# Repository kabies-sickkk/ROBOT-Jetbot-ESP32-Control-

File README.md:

# ROBOT-Jetbot-ESP32-Control-
Báo cáo đồ án môn học Đồ án IoT

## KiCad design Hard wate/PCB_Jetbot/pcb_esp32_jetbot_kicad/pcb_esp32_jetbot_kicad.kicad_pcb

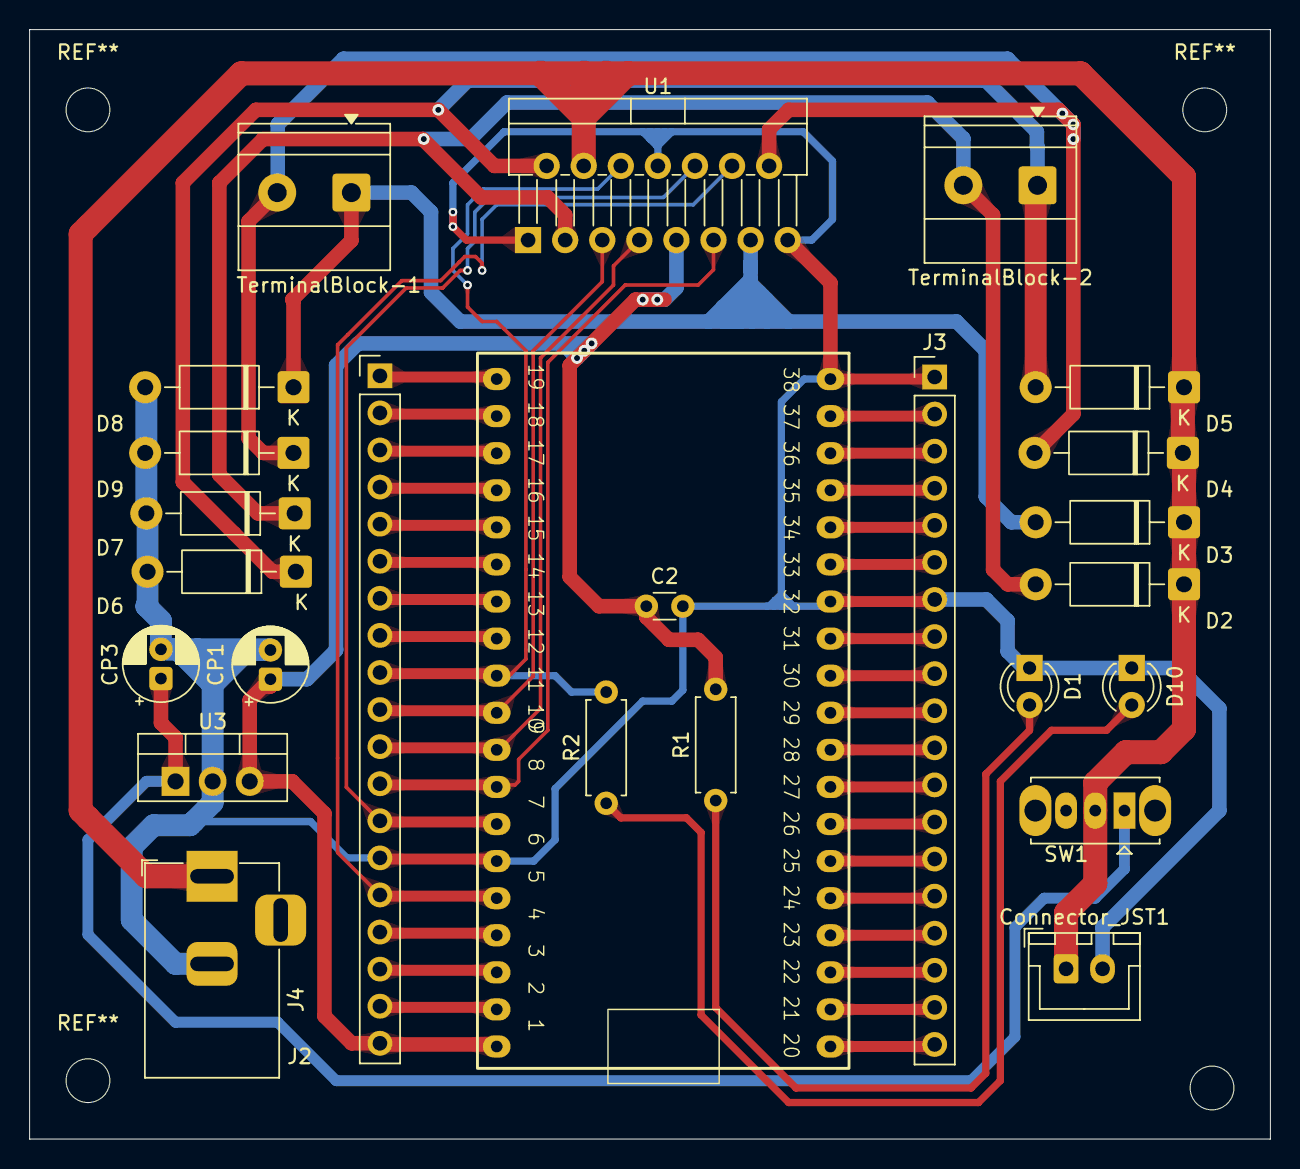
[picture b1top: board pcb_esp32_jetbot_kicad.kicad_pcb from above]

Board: 2 copper layers, 85.0 x 76.0 mm, 25 parts (0 on the bottom side), 44 nets.

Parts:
C2: 0.1uF; C_Disc_D3.0mm_W1.6mm_P2.50mm
CP1, CP3: 100uF; CP_Radial_D5.0mm_P2.00mm
Connector_JST1: JST_XH_2pin; JST_XH_B2B-XH-A_1x02_P2.50mm_Vertical
D1, D10: LED; LED_D3.0mm
D2, D3, D4, D5, D6, D7, D8, D9: D; D_DO-41_SOD81_P10.16mm_Horizontal
J2, J3: Conn_01x19_Socket; PinHeader_1x19_P2.54mm_Vertical
J4: Barrel_Jack_Switch; BarrelJack_Horizontal
R1, R2: 220Ω; R_Axial_DIN0207_L6.3mm_D2.5mm_P7.62mm_Horizontal
SW1: SW_SPDT; SW_Slide_SPDT_Straight_CK_OS102011MS2Q
TerminalBlock-1, TerminalBlock-2: Conn_01x02; TerminalBlock_Phoenix_MKDS-1,5-2-5.08_1x02_P5.08mm_Horizont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
U1: L298N; TO-220-15_P2.54x5.08mm_StaggerOdd_Lead4.58mm_Vertical
U2: ESP32-DevKitC-38; ESP32_38pin
U3: LM7805_TO220; TO-220-3_Vertical

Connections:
+3V3: J2.1, U2.19 (3.3v)
+5V: C2.1, CP1.1, J2.19, R1.2, U1.9 (Vss), U2.1 (5v), U3.3 (VO)
EN: J2.2, U2.18 (EN)
GND: C2.2, CP1.2, CP3.2, Connector_JST1.2, D1.1 (K), D6.2 (A), D7.2 (A), D8.2 (A), D9.2 (A), D10.1 (K), J2.14, J3.1, J3.7, J4.2, U1.1 (SENSE_A), U1.8 (GND), U1.15 (SENSE_B), U2.6 (GND), U2.32 (GND), U2.38 (GND), U3.2 (GND)
GPIO0: J3.14, U2.25 (GPIO0)
GPIO2: J3.15, U2.24 (GPIO2)
GPIO4: J3.13, U2.26 (GPIO4)
GPIO5: J3.10, U2.29 (GPIO5)
GPIO6: J3.19, U2.20 (GPIO6)
GPIO7: J3.18, U2.21 (GPIO7)
GPIO8: J3.17, U2.22 (GPIO8)
GPIO9: J2.16, U2.4 (GPIO9)
GPIO10: J2.17, U2.3 (GPIO10)
GPIO11: J2.18, U2.2 (GPIO11)
GPIO12: J2.13, U1.10 (IN3), U2.7 (GPIO12)
GPIO13: J2.15, U1.12 (IN4), U2.5 (GPIO13)
GPIO14: J2.12, U1.11 (EnB), U2.8 (GPIO14)
GPIO15: J3.16, U2.23 (GPIO15)
GPIO16: J3.12, U2.27 (GPIO16)
GPIO17: J3.11, U2.28 (GPIO17)
GPIO18: J3.9, U2.30 (GPIO18)
GPIO19: J3.8, U2.31 (GPIO19)
GPIO21: J3.6, U2.33 (GPIO21)
GPIO22: J3.3, U2.36 (GPIO22)
GPIO23: J3.2, U2.37 (GPIO23)
GPIO25: J2.9, R2.2, U1.6 (EnA), U2.11 (GPIO25)
GPIO26: J2.10, U1.5 (IN1), U2.10 (GPIO26)
GPIO27: J2.11, U1.7 (IN2), U2.9 (GPIO27)
GPIO32: J2.7, U2.13 (GPIO32)
GPIO33: J2.8, U2.12 (GPIO33)
GPIO34: J2.5, U2.15 (GPIO34)
GPIO35: J2.6, U2.14 (GPIO35)
GPIO36: J2.3, U2.17 (GPIO36)
GPIO39: J2.4, U2.16 (GPIO39)
unnamed: D1.2 (A), R1.1
unnamed: D2.2 (A), D7.1 (K), TerminalBlock-2.2, U1.3 (OUT2)
unnamed: D3.2 (A), D8.1 (K), TerminalBlock-1.1, U1.13 (OUT3)
unnamed: D4.2 (A), D9.1 (K), TerminalBlock-1.2, U1.14 (OUT4)
unnamed: D5.2 (A), D6.1 (K), TerminalBlock-2.1, U1.2 (OUT1)
unnamed: D10.2 (A), R2.1
unnamed: CP3.1, SW1.1 (A), U3.1 (VI)
POWER_SEL: Connector_JST1.1, D2.1 (K), D3.1 (K), D4.1 (K), D5.1 (K), J4.1, SW1.2 (B), U1.4 (Vs)
RX: J3.5, U2.34 (GPIO3)
TX: J3.4, U2.35 (GPIO1)

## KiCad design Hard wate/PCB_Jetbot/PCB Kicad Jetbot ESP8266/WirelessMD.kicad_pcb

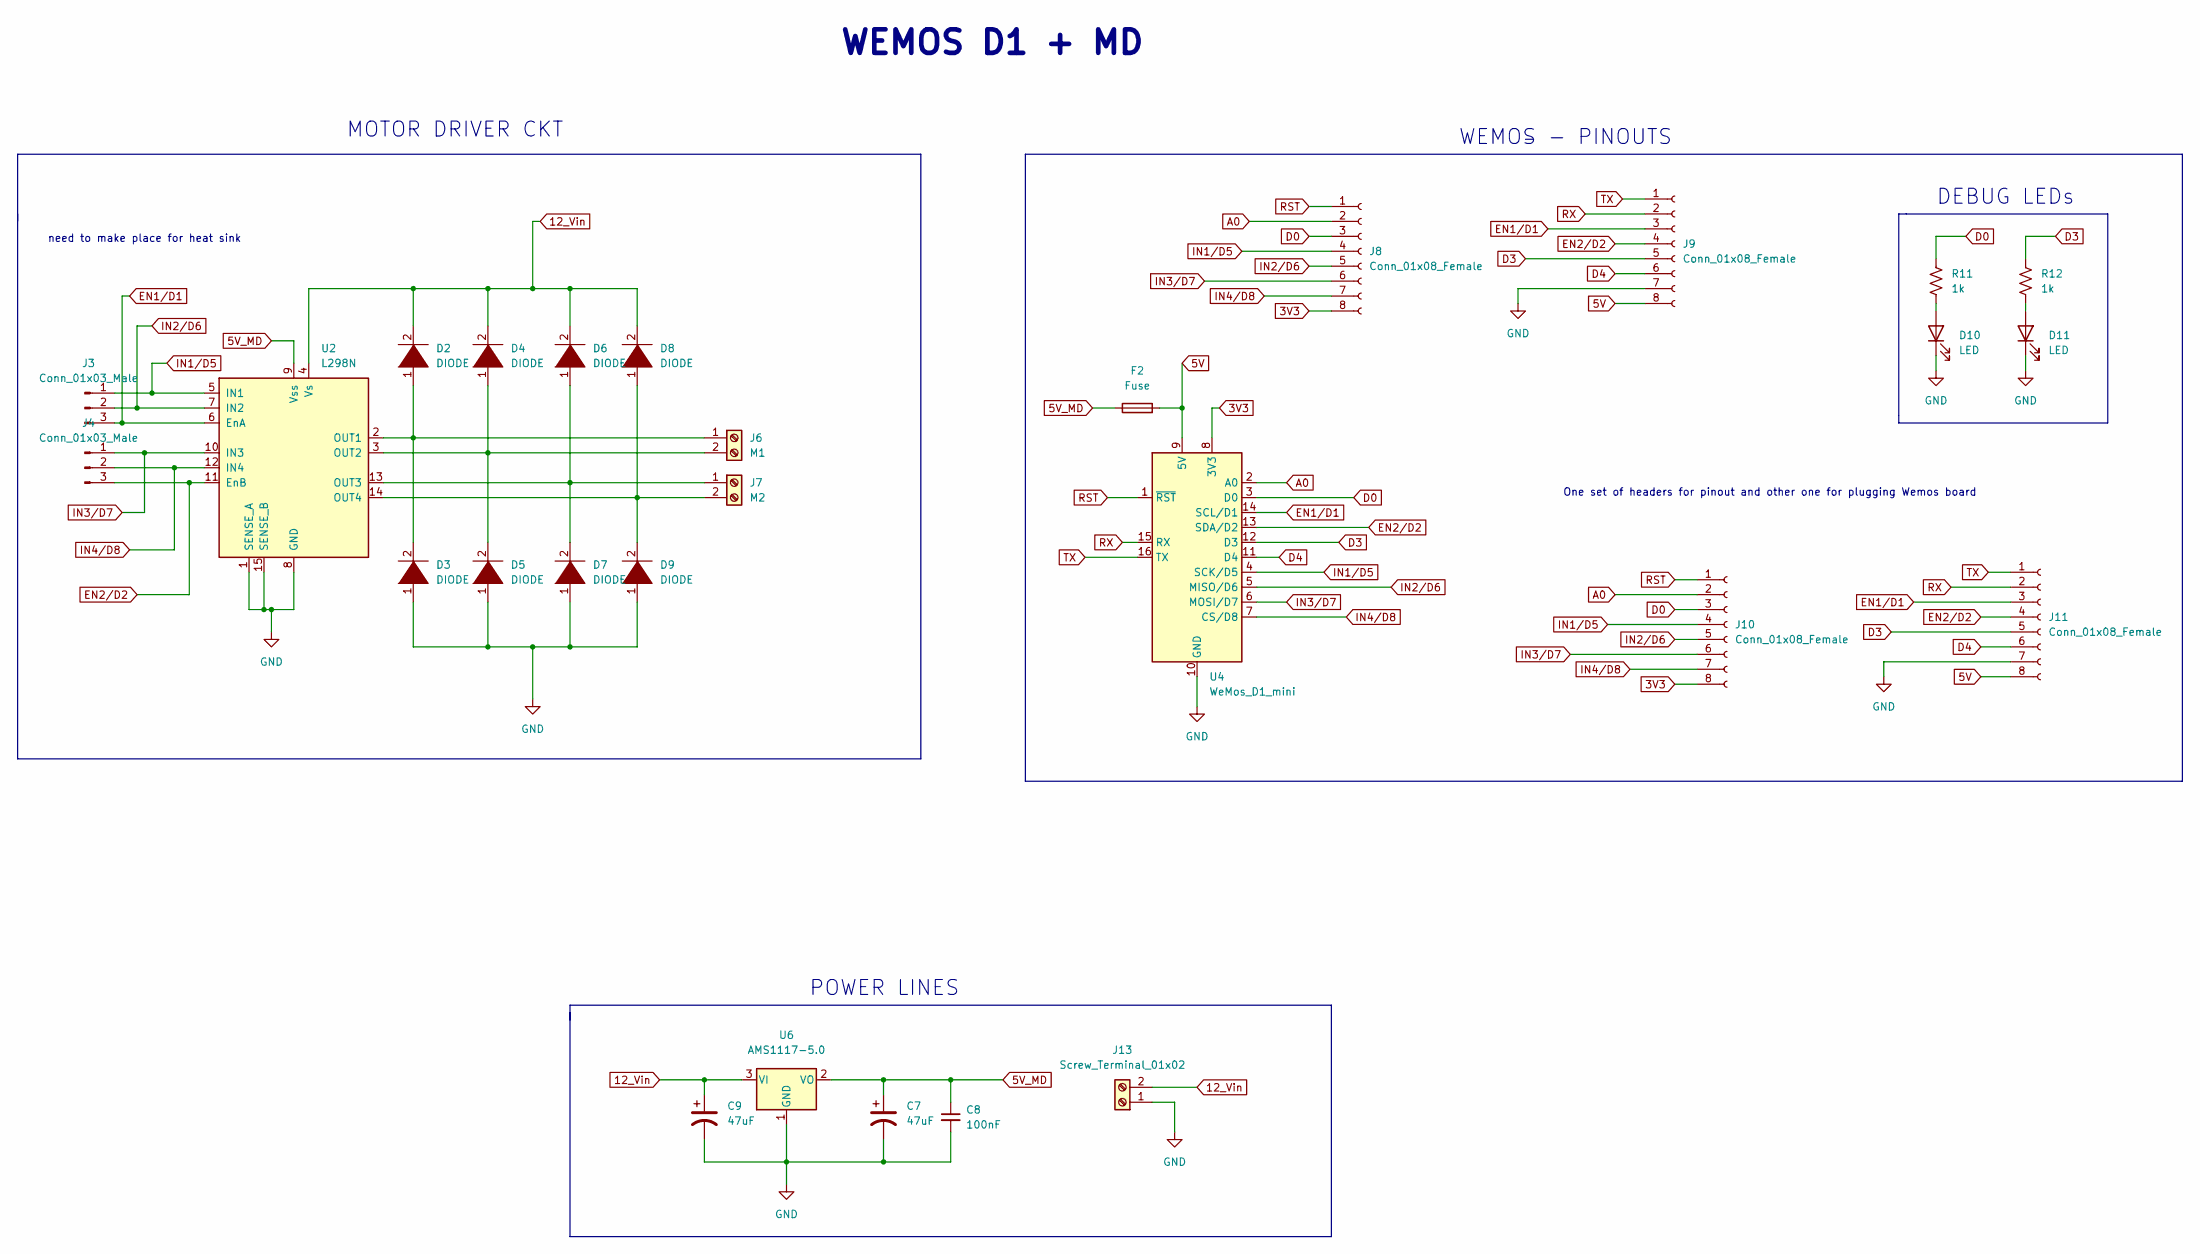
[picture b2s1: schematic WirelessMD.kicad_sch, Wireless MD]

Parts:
C7, C9: 47uF; 1206
C8: 100nF; 0805
D2, D3, D4, D5, D6, D7, D8, D9: DIODE; D_SMA_Handsoldering
D10, D11: LED; 0805
F2: Fuse; 1206
J3, J4: Conn_01x03_Male; PinHeader_1x03_P2.54mm_Vertical
J6: M1; TerminalBlock_bornier-2_P5.08mm
J7: M2; TerminalBlock_bornier-2_P5.08mm
J8, J9, J10, J11: Conn_01x08_Female; PinHeader_1x08_P2.54mm_Vertical
J13: Screw_Terminal_01x02; TerminalBlock_bornier-2_P5.08mm
R11, R12: 1k; 0805
U2: L298N; TO-220-15_P2.54x2.54mm_StaggerOdd_Lead4.58mm_Vertical
U4: WeMos_D1_mini; WEMOS_D1_mini_light
U6: AMS1117-5.0; SOT-223

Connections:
3V3: J8.8, J10.8, U4.8 (3V3)
5V: F2.2, J9.8, J11.8, U4.9 (5V)
5V_MD: C7.1, C8.1, F2.1, U2.9 (Vss), U6.2 (VO)
12_Vin: C9.1, D2.2 (A), D4.2 (A), D6.2 (A), D8.2 (A), J13.2, U2.4 (Vs), U6.3 (VI)
A0: J8.2, J10.2, U4.2 (A0)
D0: J8.3, J10.3, R11.2, U4.3 (D0)
D3: J9.5, J11.5, R12.2, U4.12 (D3)
D4: J9.6, J11.6, U4.11 (D4)
EN1/D1: J3.3, J9.3, J11.3, U2.6 (EnA), U4.14 (SCL/D1)
EN2/D2: J4.3, J9.4, J11.4, U2.11 (EnB), U4.13 (SDA/D2)
GND: C7.2, C8.2, C9.2, D3.1 (K), D5.1 (K), D7.1 (K), D9.1 (K), D10.1 (K), D11.1 (K), J9.7, J11.7, J13.1, U2.1 (SENSE_A), U2.8 (GND), U2.15 (SENSE_B), U4.10 (GND), U6.1 (GND)
IN1/D5: J3.1, J8.4, J10.4, U2.5 (IN1), U4.4 (SCK/D5)
IN2/D6: J3.2, J8.5, J10.5, U2.7 (IN2), U4.5 (MISO/D6)
IN3/D7: J4.1, J8.6, J10.6, U2.10 (IN3), U4.6 (MOSI/D7)
IN4/D8: J4.2, J8.7, J10.7, U2.12 (IN4), U4.7 (CS/D8)
unnamed: D2.1 (K), D3.2 (A), J6.1, U2.2 (OUT1)
unnamed: D4.1 (K), D5.2 (A), J6.2, U2.3 (OUT2)
unnamed: D6.1 (K), D7.2 (A), J7.1, U2.13 (OUT3)
unnamed: D8.1 (K), D9.2 (A), J7.2, U2.14 (OUT4)
unnamed: D10.2 (A), R11.1
unnamed: D11.2 (A), R12.1
RST: J8.1, J10.1, U4.1 (~RST)
RX: J9.2, J11.2, U4.15 (RX)
TX: J9.1, J11.1, U4.16 (TX)

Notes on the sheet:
POWER LINES
DEBUG LEDs
WEMOS - PINOUTS
need to make place for heat sink
MOTOR DRIVER CKT
WEMOS D1 + MD
One set of headers for pinout and other one for plugging Wemos board

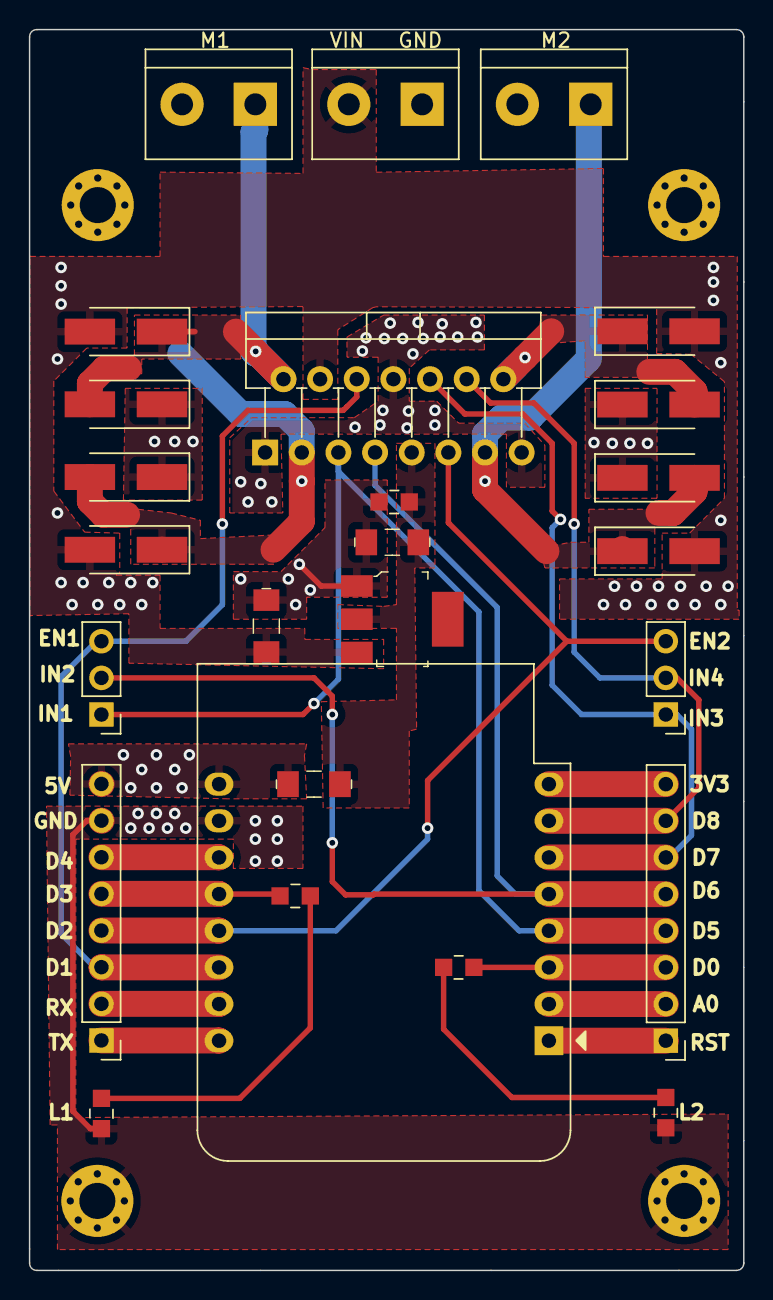
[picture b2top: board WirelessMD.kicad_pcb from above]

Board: 2 copper layers, 49.5 x 86.0 mm, 26 parts (0 on the bottom side), 24 nets.

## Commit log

2025-11-07 Create
2025-11-07 Create Hard ware
2026-01-06 code đồ án IoT
    giao diện và điều khiển mqtt và HiveMQ
2026-01-06 file báo cáo từng tuần
    file báo cao chính và file báo cáo từng tuần của môn đồ án IoT
